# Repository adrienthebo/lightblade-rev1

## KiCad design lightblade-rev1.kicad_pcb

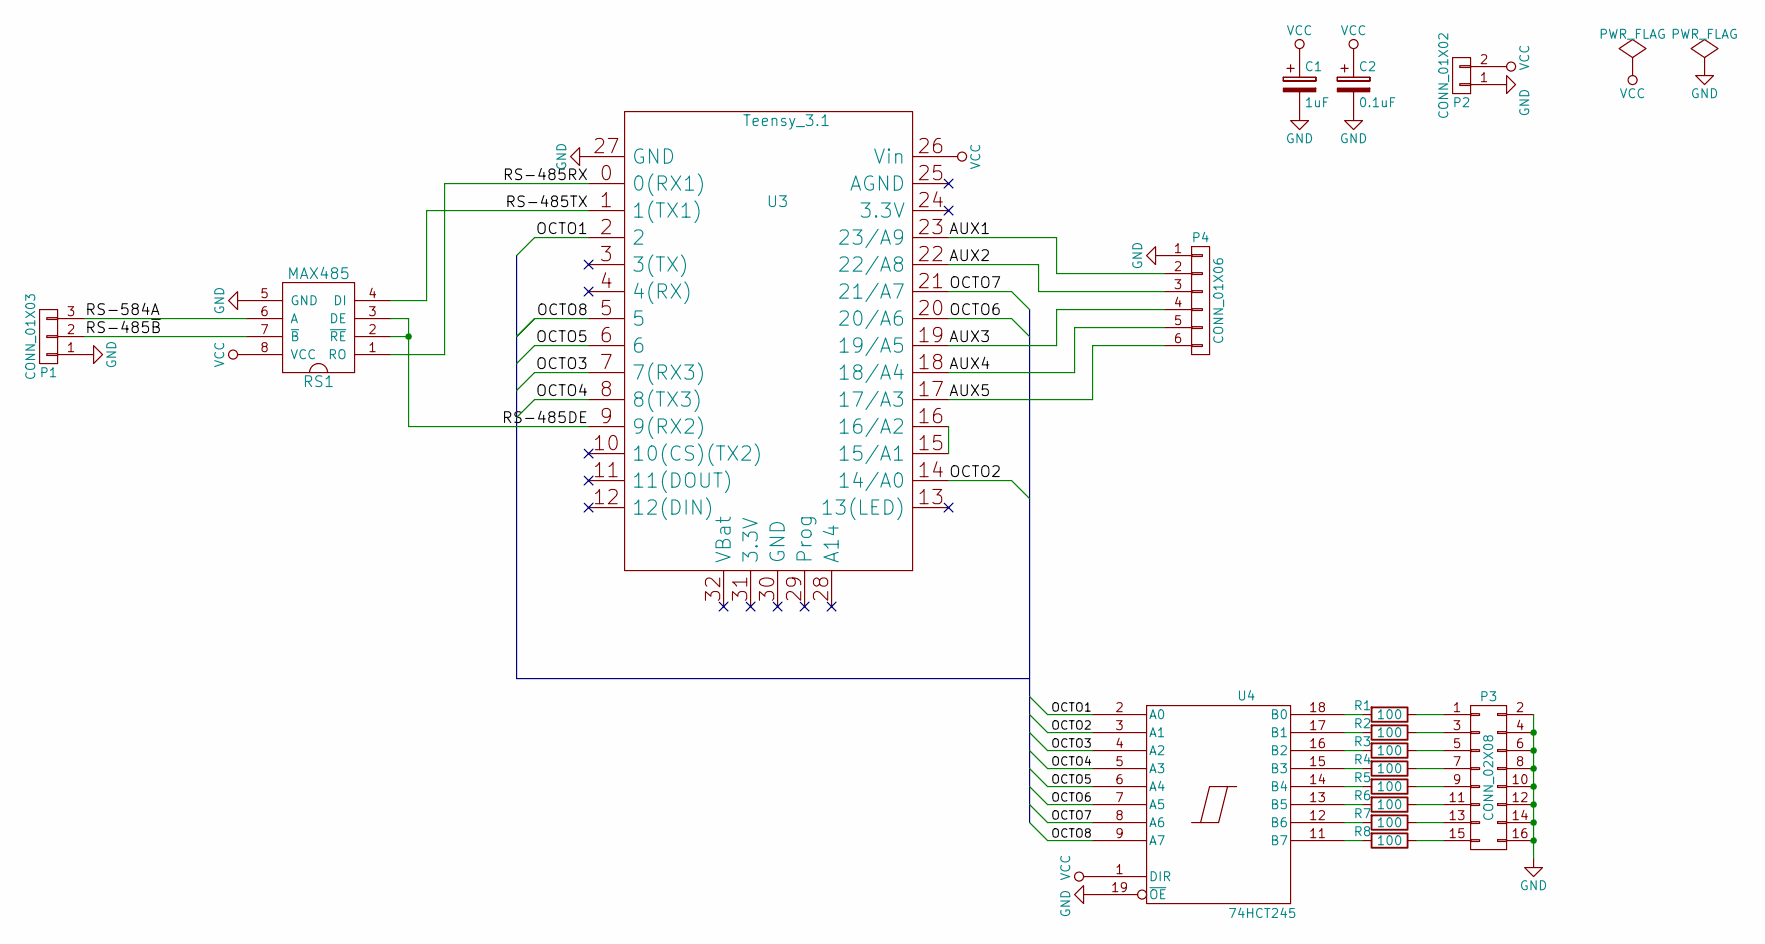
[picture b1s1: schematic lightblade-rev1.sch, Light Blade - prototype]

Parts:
C1: 1uF; C_Disc_D6_P5
C2: 0.1uF; C_Disc_D6_P5
P1: CONN_01X03; Pin_Header_Straight_1x03
P2: CONN_01X02; Pin_Header_Straight_1x02
P3: CONN_02X08; Pin_Header_Straight_2x08
P4: CONN_01X06; Pin_Header_Straight_1x06
R1, R2, R3, R4, R5, R6, R7, R8: 100; Resistor_Horizontal_RM10mm
RS1: MAX485; DIP-8_W7.62mm
U3: Teensy_3.1; Teensy-3.1
U4: 74HCT245; DIP-20_W7.62mm

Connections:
/AUX1: P4.2, U3.23 (23/A9)
/AUX2: P4.3, U3.22 (22/A8)
/AUX3: P4.4, U3.19 (19/A5)
/AUX4: P4.5, U3.18 (18/A4)
/AUX5: P4.6, U3.17 (17/A3)
/OCTO1: U3.2, U4.2 (A0)
/OCTO2: U3.14 (14/A0), U4.3 (A1)
/OCTO3: U3.7 (7(RX3)), U4.4 (A2)
/OCTO4: U3.8 (8(TX3)), U4.5 (A3)
/OCTO5: U3.6, U4.6 (A4)
/OCTO6: U3.20 (20/A6), U4.7 (A5)
/OCTO7: U3.21 (21/A7), U4.8 (A6)
/OCTO8: U3.5, U4.9 (A7)
/RS-485DE: RS1.2 (~RE), RS1.3 (DE), U3.9 (9(RX2))
/RS-485RX: RS1.1 (RO), U3.0 (0(RX1))
/RS-485TX: RS1.4 (DI), U3.1 (1(TX1))
/RS-485~B: P1.2, RS1.7 (~B)
/RS-584A: P1.3, RS1.6 (A)
GND: C1.2, C2.2, P1.1, P2.1, P3.2, P3.4, P3.6, P3.8, P3.10, P3.12, P3.14, P3.16, P4.1, RS1.5 (GND), U3.27 (GND), U4.10 (GND), U4.19 (~OE)
unnamed: P3.1, R1.1
unnamed: P3.3, R2.1
unnamed: P3.5, R3.1
unnamed: P3.7, R4.1
unnamed: P3.9, R5.1
unnamed: P3.11, R6.1
unnamed: P3.13, R7.1
unnamed: P3.15, R8.1
unnamed: R1.2, U4.18 (B0)
unnamed: R2.2, U4.17 (B1)
unnamed: R3.2, U4.16 (B2)
unnamed: R4.2, U4.15 (B3)
unnamed: R5.2, U4.14 (B4)
unnamed: R6.2, U4.13 (B5)
unnamed: R7.2, U4.12 (B6)
unnamed: R8.2, U4.11 (B7)
unnamed: U3.15 (15/A1), U3.16 (16/A2)
VCC: C1.1, C2.1, P2.2, RS1.8 (VCC), U3.26 (Vin), U4.1 (DIR), U4.20 (VCC)

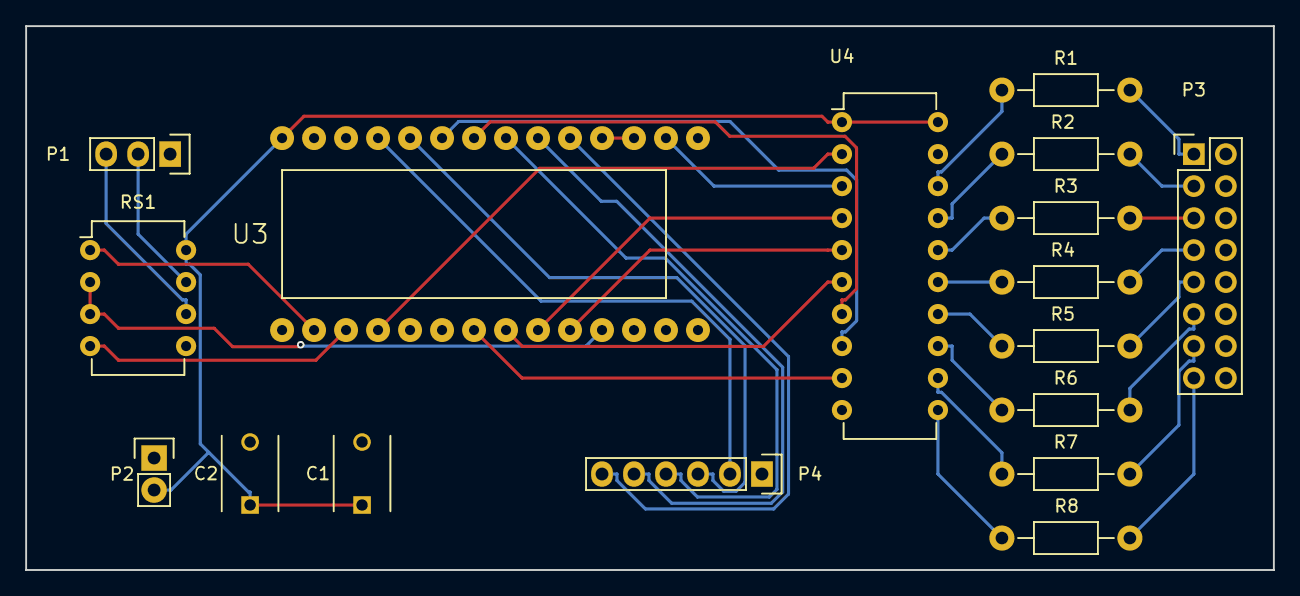
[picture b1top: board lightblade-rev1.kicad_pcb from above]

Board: 2 copper layers, 99.1 x 43.2 mm, 17 parts (0 on the bottom side), 37 nets.

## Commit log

2016-03-17 Add design
2016-03-17 check in project, schematic, supplementary libraries
2016-04-06 updates :/
2016-04-07 Update design notes
2016-04-07 copy in teensy component/footprint
2016-04-07 Initial layout
2019-10-15 Final commit before project archive
